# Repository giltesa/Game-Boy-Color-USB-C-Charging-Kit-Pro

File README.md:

# Game Boy Color USB-C Charging Kit PRO

The **Game Boy Color USB-C Charging Kit PRO** is the new circuit for **Nintendo Game Boy Color**. This time is all in one circuit and includes not only the **charging controller** but also a **boost converter** and **audio amplifier**.

The modern **IPS displays** with background light require more energy than the stock display. Also, **the flash cards** to load tons of games consume the battery very fast. If you really want to enjoy the games, the best way to do it is using a rechargeable battery instead of AA batteries.

However, that is not enough because a higher consume is forcing the original electronic to strive more than it can. That may cause noise in the speaker or headphones.

Typical solution has been adding a charging circuit for the battery and a power converter to replace the old and not efficiently one which is included in the GBC. Some people also add an audio amplifier to hear better the speaker sound. All these things make the GBC perfect, however the installation require a lot of cables and can not be easy for some people without enough knowledge.

Typical installation of the 3 modules:

*(Thanks Sascha for the photo of his installation!)*

For resolving that, this new **Game Boy Color USB-C Charging Kit PRO** includes the three circuits in one, everything wired each other, and you will just need to solder a few points to the GBC board.

## FEATURES

-   Exact shape for Game Boy Color.
-   Li-Ion battery charger by USB-C with protection for charging level and overdischarge.
-   DC to DC converter (only 5V output, not compatible with the original display).
-   Audio amplifier for the speaker with a potentiometer called VR1 to setup the maximum volume.
-   Integrated LED indicators on the main board, next to the USB for charging battery (red) and full battery (green). It can be disabled by the jumper SJ1.
-   External LED indicators board for playing (white), charging battery (red) and full battery (green). Optional installation.

## Would you like it?

https://shop.giltesa.com/product/game-boy-color-usb-c-charging-kit-pro/

## More

- [giltesa.com](https://giltesa.com "giltesa.com")
- [twitter.com](https://twitter.com/giltesa "twitter.com")

## Thankfulness

Thanks to [Zekfoo](https://github.com/Zekfoo/) for sharing his wonderful [project ](https://github.com/Zekfoo/CGZ) and solve some doubts I had. (v2.X)

Also, thanks to [lygte](https://lygte-info.dk) for his review of the IC [TP500](https://lygte-info.dk/review/Review%20Charger%20TP5000%204.2-3.6V%20module%20UK.html) (v2.X)

## License

This project is licensed under a **Creative Commons** license:
**[Attribution-NonCommercial-ShareAlike 4.0 International (CC BY-NC-SA 4.0) ](https://creativecommons.org/licenses/by-nc-sa/4.0/)**

Check the [LICENSE.md](LICENSE.md) for more information.

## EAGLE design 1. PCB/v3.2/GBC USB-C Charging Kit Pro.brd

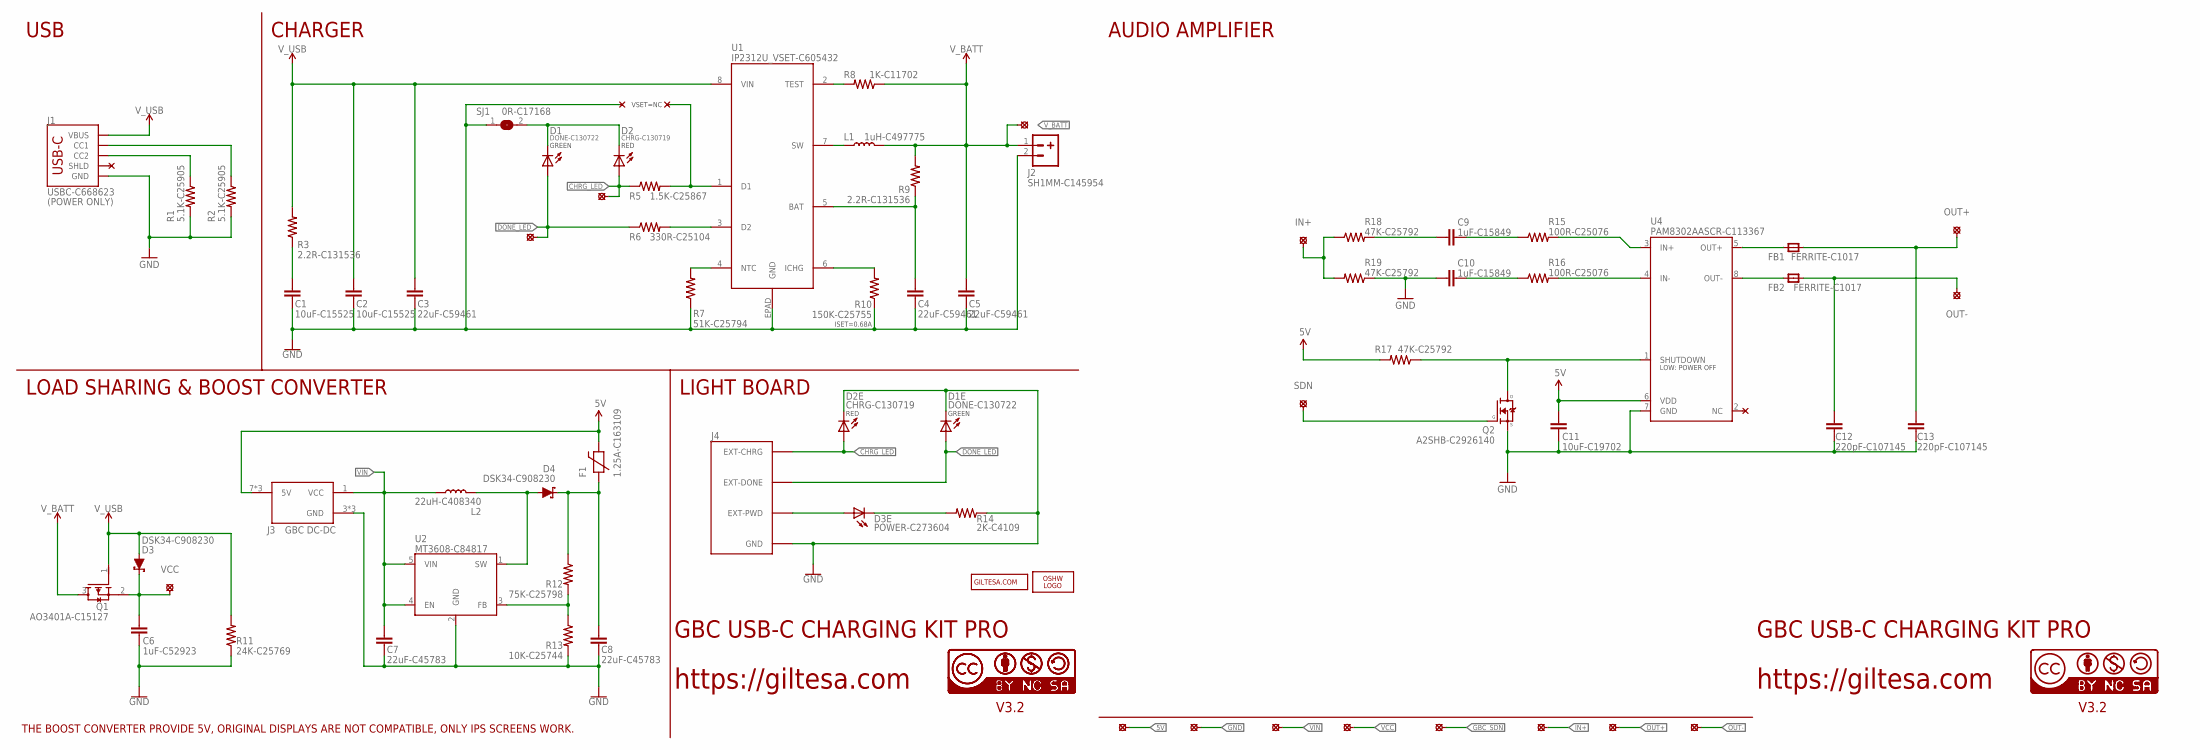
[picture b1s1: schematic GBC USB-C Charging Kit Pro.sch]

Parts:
C1, C2: 10uF-C15525; C0402_S
C3, C4, C5: 22uF-C59461; C0603_S
C6: 1uF-C52923; C0402_S
C7, C8: 22uF-C45783; C0805_S
C9, C10: 1uF-C15849; C0603_S
C11: 10uF-C19702; C0603_S
C12, C13: 220pF-C107145; C0805_S
D1, D1E: DONE-C130722; L0402
D2, D2E: CHRG-C130719; L0402
D3, D4: DSK34-C908230; SOD-123FL
D3E: POWER-C273604; L0402
F1: 1.25A-C163109; F0603_S
FB1, FB2: FERRITE-C1017; MICROBUILDER__0805MP_S
J1: USBC-C668623; USB-C_6P
J2: SH1MM-C145954; JST-2-1MM-SMD_RIGHT
J3: GBC DC-DC; GBC_DC_DC_DIP_V2
J4: GBC_LED_V2
L1: 1uH-C497775; PSPMAA0402
L2: 22uH-C408340; PSPMAA0402
LOGO2: OSHW_LOGO_FILLX0150-NT; OSHW_FILLX150_NOTEXT
PP1, PP2, PP3, PP4, PP5, PP6, PP7, PP8: SOLDER_PAD-1.5; SOLDER_PAD_1.5
Q1: AO3401A-C15127; SOT23-3_S
Q2: A2SHB-C2926140; SOT23-3_S
R1, R2: 5.1K-C25905; R0402
R3, R9: 2.2R-C131536; R0402
R5: 1.5K-C25867; R0402
R6: 330R-C25104; R0402
R7: 51K-C25794; R0402
R8: 1K-C11702; R0402
R10: 150K-C25755; R0402
R11: 24K-C25769; R0402
R12: 75K-C25798; R0402
R13: 10K-C25744; R0402
R14: 2K-C4109; R0402
R15, R16: 100R-C25076; R0402
R17, R18, R19: 47K-C25792; R0402
SJ1: 0R-C17168; JUMPER-SMD_0402
U1: IP2312U_VSET-C605432; IP2312
U2: MT3608-C84817; SOT-23-6
U4: PAM8302AASCR-C113367; PAM8302AASCR
U$1: VCC; PAD_1.25
U$2: SDN; PAD_1.0
U$3, U$24: CHRG_LED; SOLDER_PAD_1.3
U$6: CC-BY-NC-SA15MM; CC-BY-NC-SA_15MM
U$16: GILTESA.COM_MASK; GILTESA.COM_MASK_15MM
U$17, U$21: CC-NC-BCNIX; CC-NC-B_NIX
U$20: OUT+; SOLDER_PAD_2.0
U$23: OUT-; SOLDER_PAD_2.0
U$25: DONE_LED; SOLDER_PAD_1.3
U$30: IN+; SOLDER_PAD_1.3

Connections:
5V: C11.1, F1.2, J3.7 (5V), J3.7_1 (5V), J3.7_2 (5V), PP1.P$1, R17.2, U4.6 (VDD)
CHRG_LED: D2.A, D2E.A, J4.EXT-CHRG, R5.1, U$24.P$1
DONE_LED: D1.A, D1E.A, J4.EXT-DONE, R6.1, U$25.P$1
GBC_SDN: PP5.P$1, Q2.1 (G), U$2.P$1
GND: C1.1, C2.1, C3.1, C4.1, C5.1, C6.2, C7.1, C8.1, C10.2, C11.2, C12.2, C13.2, D1E.C, D2E.C, J1.A12-GND (GND), J1.B12-GND (GND), J2.2, J3.3 (GND), J3.3_1 (GND), J3.3_2 (GND), J4.GND, PP2.P$1, Q2.2 (S), R1.2, R2.2, R7.1, R10.1, R11.1, R13.2, R14.1, R19.1, SJ1.1, U1.EPAD (GND), U2.2 (GND), U4.7 (GND)
IN+: PP6.P$1, R18.1, R19.2, U$30.P$1
unnamed: D1.C, D2.C, SJ1.2
unnamed: C8.2, D4.C, F1.1, R12.1
unnamed: D4.A, L2.P$2 (2), U2.1 (SW)
unnamed: J1.B5 (CC2), R1.1
unnamed: R8.2, U1.2 (TEST)
unnamed: R12.2, R13.1, U2.3 (FB)
unnamed: R16.2, U4.4 (IN-)
unnamed: D3E.A, J4.EXT-PWD
unnamed: D3E.C, R14.2
unnamed: R15.2, U4.3 (IN+)
unnamed: J1.A5 (CC1), R2.1
unnamed: C4.2, R9.1, U1.5 (BAT)
unnamed: C1.2, R3.1
unnamed: C10.1, R16.1
unnamed: FB2.1, U4.8 (OUT-)
unnamed: R5.2, U1.1 (D1)
unnamed: FB1.1, U4.5 (OUT+)
unnamed: C9.1, R15.1
unnamed: C9.2, R18.2
unnamed: R7.2, U1.4 (NTC)
unnamed: R10.2, U1.6 (ICHG)
unnamed: R6.2, U1.3 (D2)
unnamed: L1.P$1 (1), U1.7 (SW)
OUT+: C13.1, FB1.2, PP7.P$1, U$20.P$1
OUT-: C12.1, FB2.2, PP8.P$1, U$23.P$1
SDN: Q2.3 (D), R17.1, U4.1 (SHUTDOWN)
VCC: C6.1, D3.C, PP4.P$1, Q1.2 (S), U$1.P$1
VIN: C7.2, J3.1 (VCC), L2.P$1 (1), PP3.P$1, U2.4 (EN), U2.5 (VIN)
V_BATT: C5.2, J2.1, L1.P$2 (2), Q1.3 (D), R8.1, R9.2, U$3.P$1
V_USB: C2.2, C3.2, D3.A, J1.A9-VBUS (VBUS), J1.B9-VBUS (VBUS), Q1.1 (G), R3.2, R11.2, U1.8 (VIN)

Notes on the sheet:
GBC USB-C CHARGING KIT PRO
https://giltesa.com
V3.2
(POWER ONLY)
THE BOOST CONVERTER PROVIDE 5V, ORIGINAL DISPLAYS ARE NOT COMPATIBLE, ONLY IPS SCREENS WORK.
USB
CHARGER
LOAD SHARING & BOOST CONVERTER
AUDIO AMPLIFIER
LIGHT BOARD
ISET=0.68A
GREEN
RED
VSET=NC

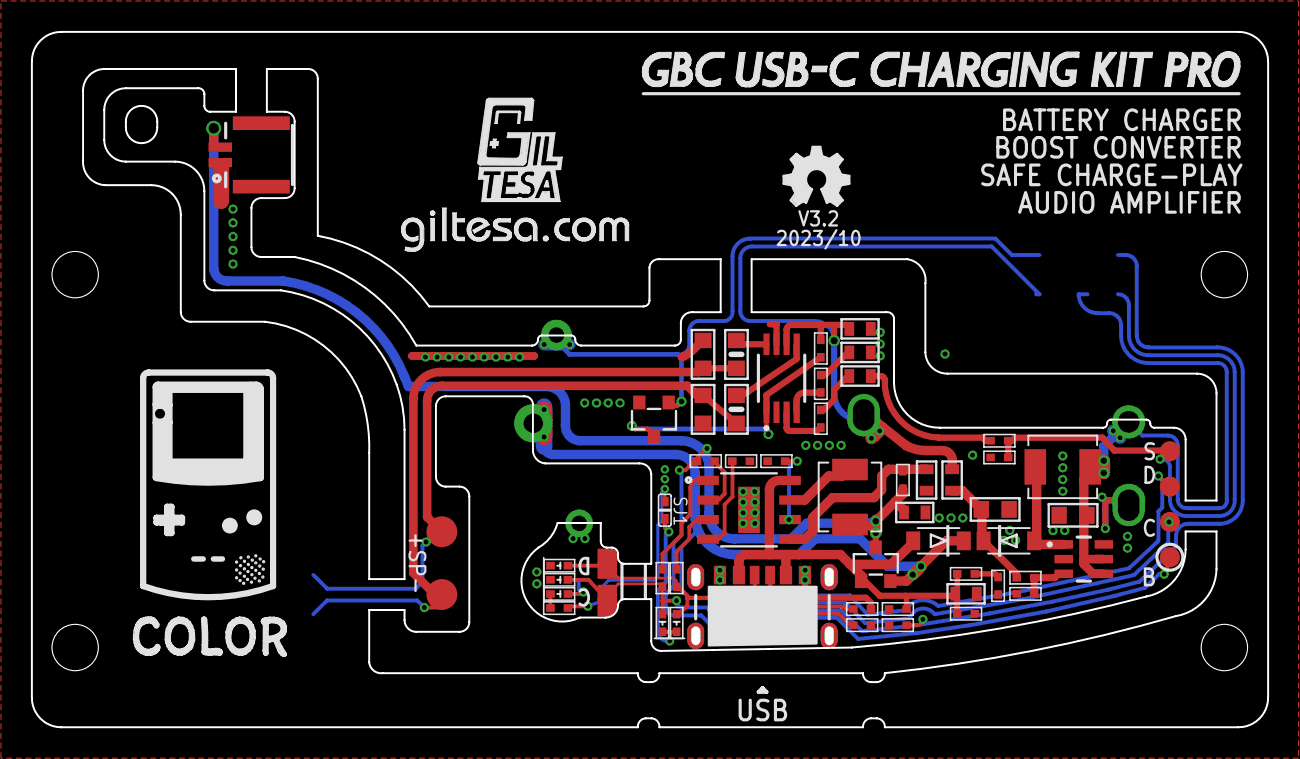
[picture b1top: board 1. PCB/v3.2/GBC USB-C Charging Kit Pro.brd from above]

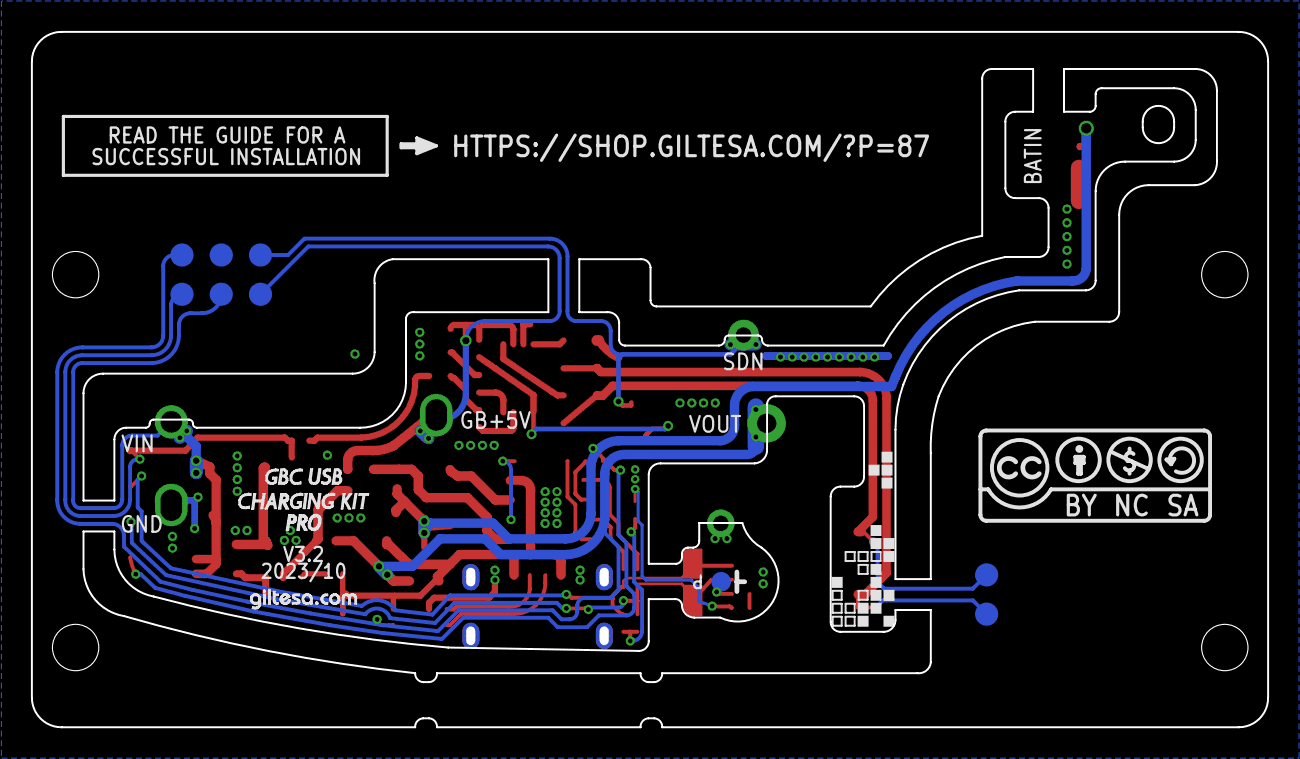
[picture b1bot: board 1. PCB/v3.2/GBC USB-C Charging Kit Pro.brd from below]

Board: 2 copper layers, 80.0 x 45.0 mm, 80 parts (11 on the bottom side), 36 nets.

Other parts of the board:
U$7: GBC_FRAME_LOGO
U$9: GILTESA_LOGO_MASK_7MM
U$10: TETRIS
U$12: GBC_PRO_FRAME
U$33: GILTESA.COM_MASK_7MM@1
U$34: GAME_BOY_COLOR_USB_CHARGING_KIT_PRO

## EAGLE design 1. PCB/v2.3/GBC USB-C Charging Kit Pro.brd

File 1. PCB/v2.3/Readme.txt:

2023-02-12: GBC PRO v2.3

It recently has been detected a strange malfunction
that can occur only in this specific situation and not always,
it happens occasionally:

    With the GBC turned off, you plug in the USB-C cable and then power on the GBC.
    Occasionally the red light will turn off just after the GBC is turned on,
    and then the charging circuit will get very hot until it is damaged.

    It works properly when the GBC is already on and then the USB-C cable is connected.
    Or when the GBC is charging but it remains off.
    https://www.youtube.com/watch?v=xmc3yf6yNuk

However, I highly recommend not charging and playing at the same time to avoid any problem
(like the previous version which didn’t support it).

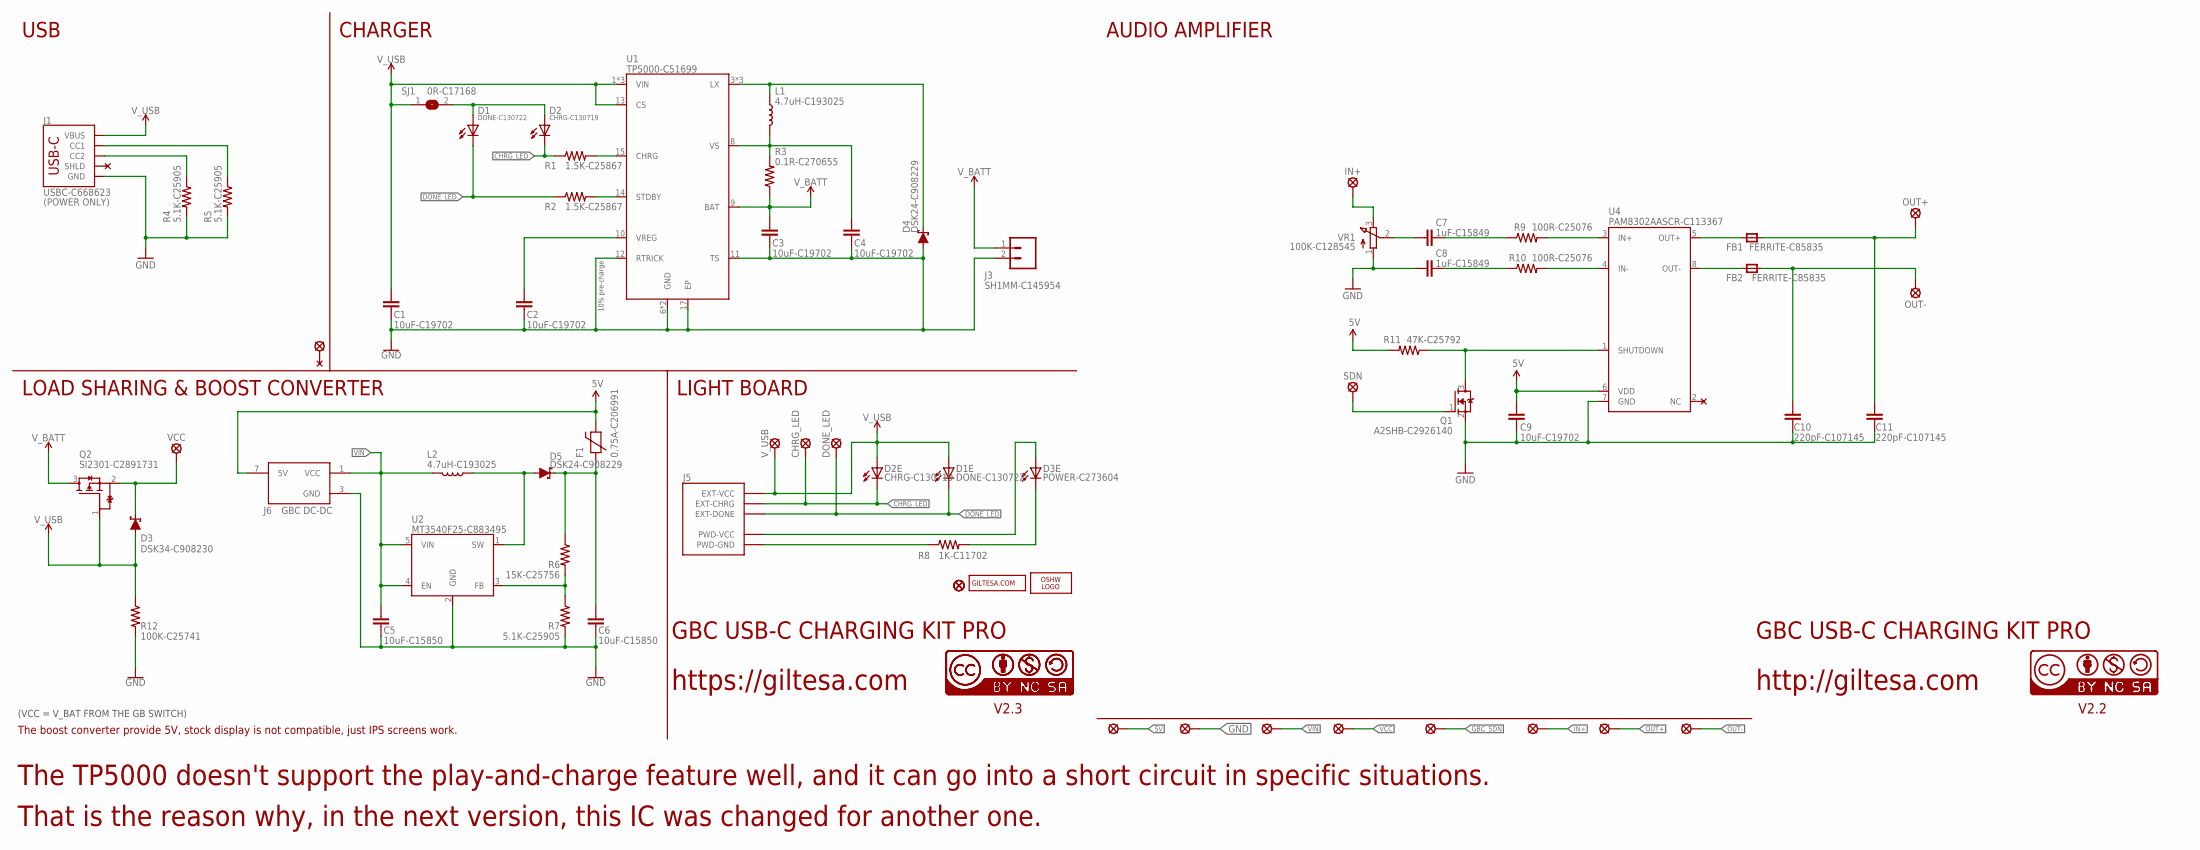
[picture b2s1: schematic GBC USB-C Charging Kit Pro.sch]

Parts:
C1, C2, C3, C4, C9: 10uF-C19702; C0603_S
C5, C6: 10uF-C15850; C0805_S
C7, C8: 1uF-C15849; C0603_S
C10, C11: 220pF-C107145; C0805_S
D1, D1E: DONE-C130722; L0402
D2, D2E: CHRG-C130719; L0402
D3: DSK34-C908230; SOD-123FL
D3E: POWER-C273604; L0402
D4, D5: DSK24-C908229; SOD-123FL
F1: 0.75A-C206991; F0603_S
FB1, FB2: FERRITE-C85835; MICROBUILDER__0805MP_S
FD1, FD2, FD3: FIDUCIALUFIDUCIAL; FIDUCIAL-MICRO
J1: USBC-C668623; USB-C_6P
J3: SH1MM-C145954; JST-2-1MM-SMD_RIGHT
J5: GBC_LED
J6: GBC DC-DC; GBC_DC_DC_DIP
L1, L2: 4.7uH-C193025; PSPMAA0402
LOGO2: OSHW_LOGO_FILLX0150-NT; OSHW_FILLX150_NOTEXT
PP1, PP2, PP3, PP4, PP5, PP6, PP7, PP8: SOLDER_PAD-1.5; SOLDER_PAD_1.5
Q1: A2SHB-C2926140; SOT23-3_S
Q2: SI2301-C2891731; SOT23-3_S
R1, R2: 1.5K-C25867; R0402
R3: 0.1R-C270655; R0402
R4, R5, R7: 5.1K-C25905; R0402
R6: 15K-C25756; R0402
R8: 1K-C11702; R0402
R9, R10: 100R-C25076; R0402
R11: 47K-C25792; R0402
R12: 100K-C25741; R0402
SJ1: 0R-C17168; JUMPER-SMD_0402
U1: TP5000-C51699; QFN-16_4X4
U2: MT3540F25-C883495; SOT-23-5
U4: PAM8302AASCR-C113367; PAM8302AASCR
U$2: SDN; PAD_1.0
U$6: CC-BY-NC-SA15MM; CC-BY-NC-SA_15MM
U$16: GILTESA.COM_MASK
U$17, U$21: CC-NC-BCNIX; CC-NC-B_NIX
U$20: OUT+; SOLDER_PAD_2.0
U$23: OUT-; SOLDER_PAD_2.0
U$24: CHRG_LED; SOLDER_PAD_1.3
U$25: DONE_LED; SOLDER_PAD_1.3
U$26: V_USB; SOLDER_PAD_1.3
U$29: VCC; PAD_1.25
U$30: IN+; SOLDER_PAD_1.3
U$32: SOLDER_PAD-2.5; SOLDER_PAD_2.5
VR1: 100K-C128545; TRIMPOT_BOURNS_3303W

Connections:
5V: C9.1, F1.2, J6.7 (5V), PP1.P$1, R11.2, U4.6 (VDD)
CHRG_LED: D2.C, D2E.C, J5.EXT-CHRG, R1.1, U$24.P$1
DONE_LED: D1.C, D1E.C, J5.EXT-DONE, R2.1, U$25.P$1
GBC_SDN: PP5.P$1, Q1.1 (G), U$2.P$1
GND: C1.1, C2.1, C3.1, C4.1, C5.1, C6.1, C8.2, C9.2, C10.2, C11.2, D4.A, J1.GND1 (GND), J1.GND2 (GND), J3.2, J6.3 (GND), PP2.P$1, Q1.2 (S), R4.2, R5.2, R7.2, R12.2, U1.6 (GND), U1.7 (GND), U1.11 (TS), U1.12 (RTRICK), U1.17 (EP), U2.2 (GND), U4.7 (GND), VR1.1 (A)
IN+: PP6.P$1, U$30.P$1, VR1.3 (E)
unnamed: D1.A, D2.A, SJ1.2
unnamed: C6.2, D5.C, F1.1, R6.1
unnamed: D5.A, L2.P$1 (1), U2.1 (SW)
unnamed: J1.B5 (CC2), R4.1
unnamed: R1.2, U1.15 (CHRG)
unnamed: R6.2, R7.1, U2.3 (FB)
unnamed: J5.PWD-GND, R8.1
unnamed: R10.2, U4.4 (IN-)
unnamed: D3E.A, J5.PWD-VCC
unnamed: D3E.C, R8.2
unnamed: R9.2, U4.3 (IN+)
unnamed: J1.A5 (CC1), R5.1
unnamed: C8.1, R10.1
unnamed: FB2.1, U4.8 (OUT-)
unnamed: C2.2, U1.10 (VREG)
unnamed: R2.2, U1.14 (STDBY)
unnamed: C4.2, L1.P$2 (2), R3.2, U1.8 (VS)
unnamed: D4.C, L1.P$1 (1), U1.3 (LX), U1.4 (LX), U1.5 (LX)
unnamed: FB1.1, U4.5 (OUT+)
unnamed: C7.1, R9.1
unnamed: C7.2, VR1.2 (S)
OUT+: C11.1, FB1.2, PP7.P$1, U$20.P$1
OUT-: C10.1, FB2.2, PP8.P$1, U$23.P$1
SDN: Q1.3 (D), R11.1, U4.1 (SHUTDOWN)
VCC: D3.C, PP4.P$1, Q2.2 (S), U$29.P$1
VIN: C5.2, J6.1 (VCC), L2.P$2 (2), PP3.P$1, U2.4 (EN), U2.5 (VIN)
V_BATT: C3.2, J3.1, Q2.3 (D), R3.1, U1.9 (BAT)
V_USB: C1.2, D1E.A, D2E.A, D3.A, J1.VBUS1 (VBUS), J1.VBUS2 (VBUS), J5.EXT-VCC, Q2.1 (G), R12.1, SJ1.1, U1.1 (VIN), U1.2 (VIN), U1.13 (CS), U1.16 (VIN), U$26.P$1

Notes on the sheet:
GBC USB-C CHARGING KIT PRO
https://giltesa.com
V2.3
(POWER ONLY)
The boost converter provide 5V, stock display is not compatible, just IPS screens work.
(VCC = V_BAT FROM THE GB SWITCH)
USB
CHARGER
LOAD SHARING & BOOST CONVERTER
AUDIO AMPLIFIER
http://giltesa.com
V2.2
10% pre-charge
LIGHT BOARD
The TP5000 doesn't support the play-and-charge feature well, and it can go into a short circuit in specific situations.
That is the reason why, in the next version, this IC was changed for another one.

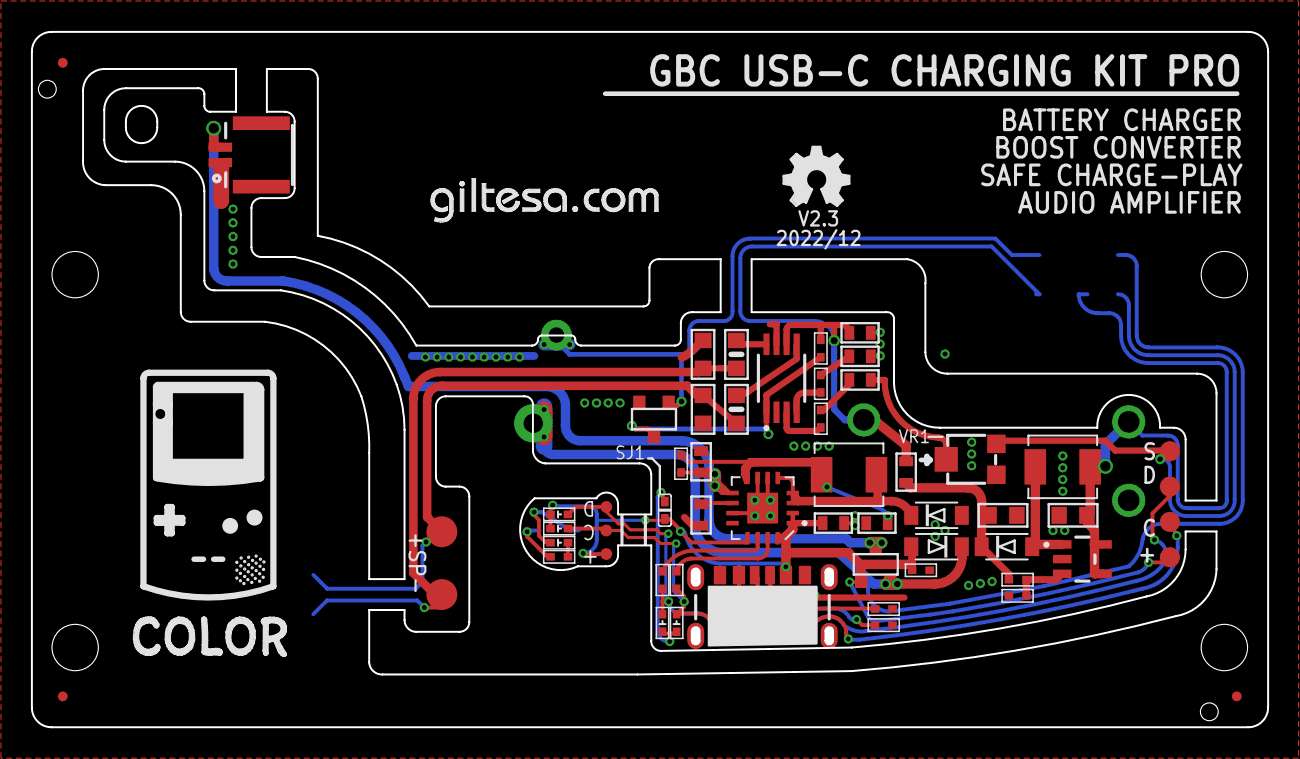
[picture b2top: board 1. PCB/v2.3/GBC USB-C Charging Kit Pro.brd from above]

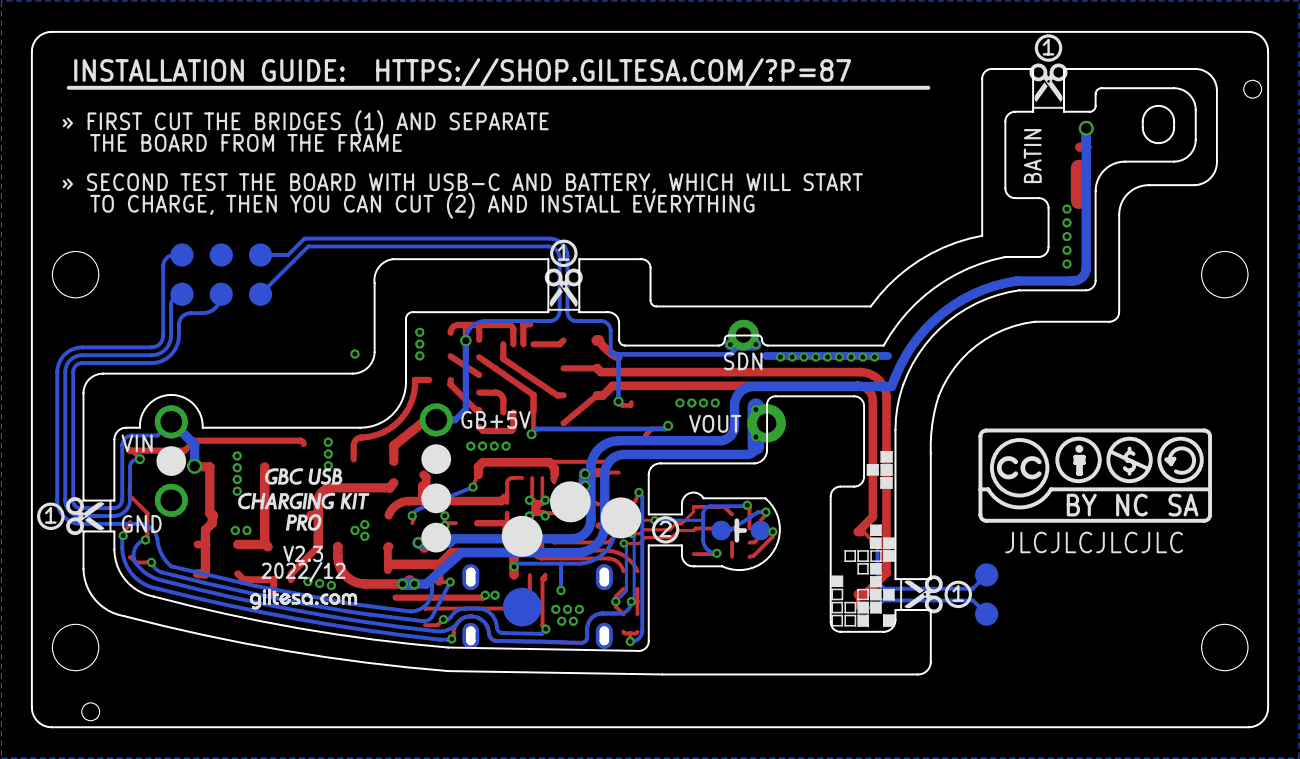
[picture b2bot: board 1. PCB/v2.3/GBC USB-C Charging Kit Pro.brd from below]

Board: 2 copper layers, 80.0 x 45.0 mm, 88 parts (21 on the bottom side), 34 nets.

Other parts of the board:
U$7: GAME_BOY_COLOR_1.2
U$8, U$13, U$14, U$15: SCISSOR
U$10: TETRIS
U$12, U$18: JLCPCB_TOOLING_HOLES
U$28: GAME_BOY_COLOR_2
U$33: GILTESA.COM_MASK_7MM
U$34: GAME_BOY_COLOR_USB_CHARGING_KIT_PRO
U$36, U$37, U$38, U$39: SCISSOR_ONE
U$40: SCISSOR_TWO

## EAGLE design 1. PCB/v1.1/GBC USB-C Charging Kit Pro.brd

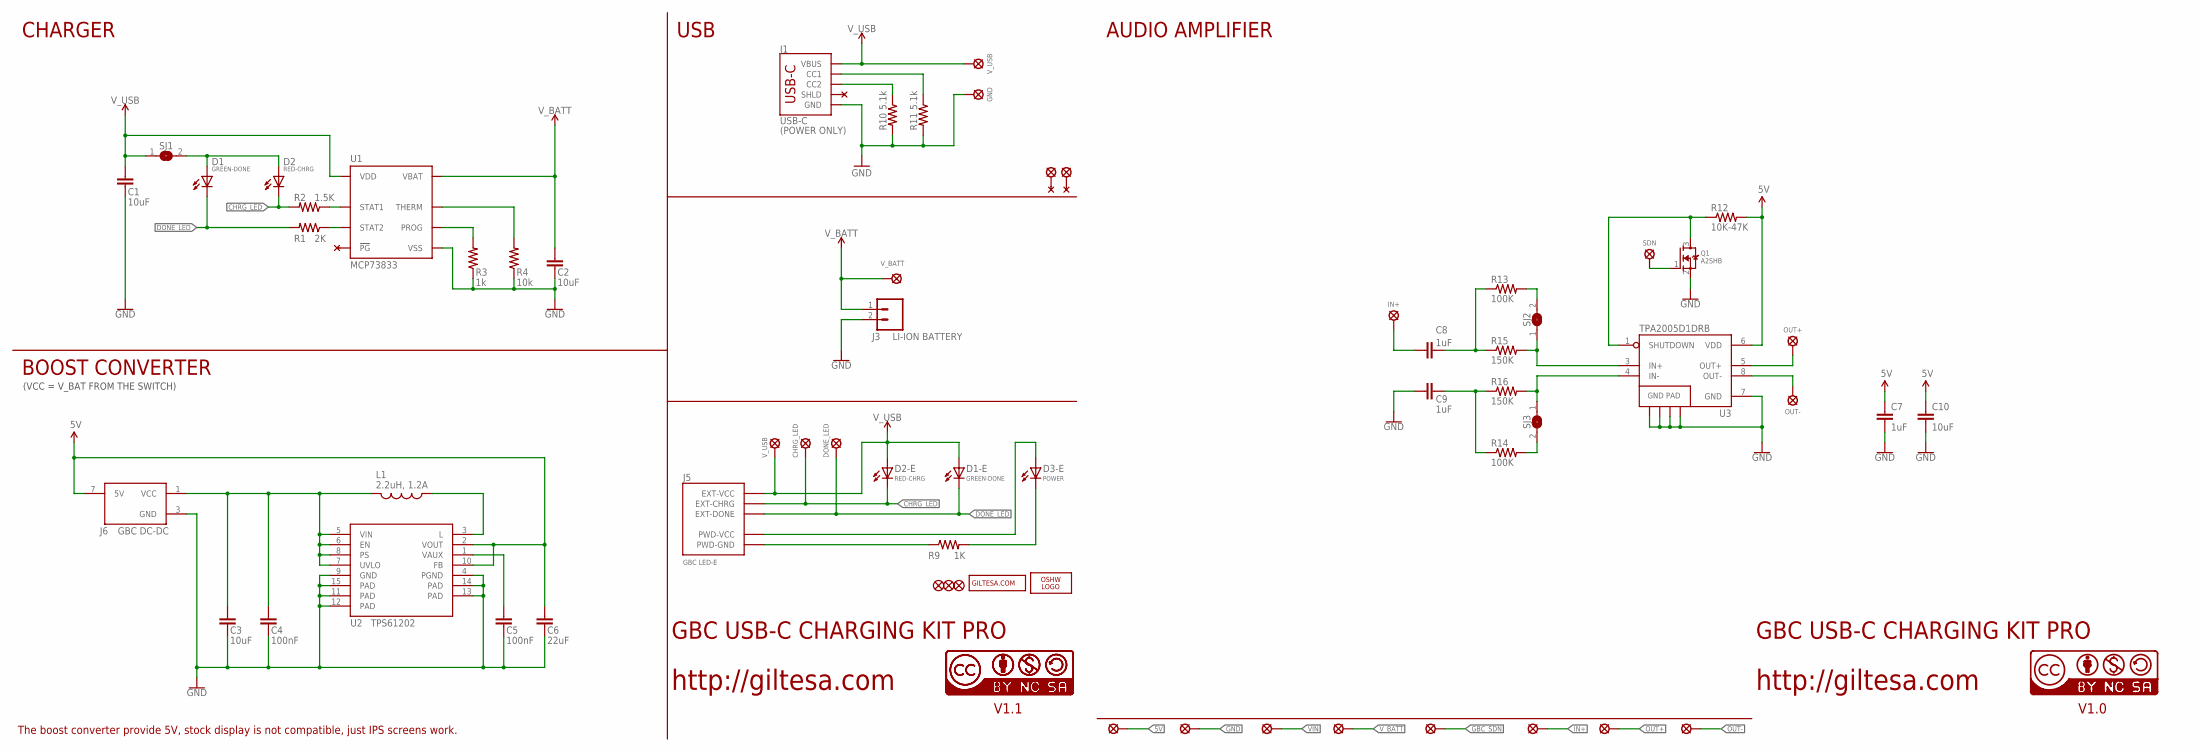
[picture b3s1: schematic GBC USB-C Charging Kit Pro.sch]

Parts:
C1, C2: 10uF; C0603
C3, C10: 10uF; C1206
C4, C5: 100nF; C0603
C6: 22uF; C0805_S
C7: 1uF; C1206
C8, C9: 1uF; C0402
D1, D1-E: GREEN-DONE; L0402
D2, D2-E: RED-CHRG; L0402
D3-E: POWER; L0402
FD2, FD3, FD4: FIDUCIALUFIDUCIAL; FIDUCIAL-MICRO
J1: USB-C; USB-C_6P
J3: LI-ION BATTERY; JST-2-1MM-SMD_RIGHT
J5: GBC LED-E; GBC_LED
J6: GBC DC-DC; GBC_DC_DC_DIP
L1: 2.2uH, 1.2A; CDRH2D09
LOGO2: OSHW_LOGO_FILLX0150-NT; OSHW_FILLX150_NOTEXT
PP1, PP2, PP3, PP4, PP5, PP6, PP7, PP8: SOLDER_PAD-1.5; SOLDER_PAD_1.5
Q1: A2SHB; SOT23
R1: 2K; R0402
R2: 1.5K; R0402
R3: 1k; R0402
R4: 10k; R0402
R9: 1K; R0402
R10, R11: 5.1k; R0402
R12: 10K-47K; R0402
R13, R14: 100K; R0402
R15, R16: 150K; R0402
SJ1, SJ2, SJ3: JUMPER-SMD0402; JUMPER-SMD_0402
U1: MCP73833; DFN-10
U2: TPS61202; QFN-10_PAD
U3: TPA2005D1DRB; QFN-8_PAD
U$1: V_USB; SOLDER_PAD_1.5
U$2: SDN; PAD_1.0
U$3: GND; SOLDER_PAD_1.5
U$6: CC-BY-NC-SA15MM; CC-BY-NC-SA_15MM
U$9, U$32: SOLDER_PAD-2.5; SOLDER_PAD_2.5
U$16: GILTESA.COM_MASK
U$17, U$21: CC-NC-BCNIX; CC-NC-B_NIX
U$20: OUT+; SOLDER_PAD_2.0
U$23: OUT-; SOLDER_PAD_2.0
U$24: CHRG_LED; SOLDER_PAD_1.3
U$25: DONE_LED; SOLDER_PAD_1.3
U$26: V_USB; SOLDER_PAD_1.3
U$29: V_BATT; PAD_1.25
U$30: IN+; SOLDER_PAD_1.3

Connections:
5V: C6.1, C7.1, C10.1, J6.7 (5V), PP1.P$1, R12.2, U2.2 (VOUT), U2.10 (FB), U3.6 (VDD)
CHRG_LED: D2.C, D2-E.C, J5.EXT-CHRG, R2.2, U$24.P$1
DONE_LED: D1.C, D1-E.C, J5.EXT-DONE, R1.2, U$25.P$1
GBC_SDN: PP5.P$1, Q1.1 (G), U$2.P$1
GND: C1.2, C2.2, C3.2, C4.2, C5.2, C6.2, C7.2, C9.1, C10.2, J1.GND1 (GND), J1.GND2 (GND), J3.2, J6.3 (GND), PP2.P$1, Q1.2 (S), R3.1, R4.1, R10.2, R11.2, U1.P$5 (VSS), U1.P$11 (VSS), U2.4 (PGND), U2.9 (GND), U2.11 (PAD), U2.12 (PAD), U2.13 (PAD), U2.14 (PAD), U2.15 (PAD), U3.7 (GND), U3.10 (GND), U3.11 (GND), U3.12 (GND), U3.13 (GND), U$3.P$1
IN+: C8.1, PP6.P$1, U$30.P$1
IN+AMP: R15.2, SJ2.1, U3.3 (IN+)
IN-AMP: R16.2, SJ3.1, U3.4 (IN-)
unnamed: D1.A, D2.A, SJ1.2
unnamed: R13.2, SJ2.2
unnamed: L1.P$1 (1), U2.3 (L)
unnamed: J1.B5 (CC2), R10.1
unnamed: R14.2, SJ3.2
unnamed: C5.1, U2.1 (VAUX)
unnamed: J5.PWD-GND, R9.1
unnamed: D3-E.A, J5.PWD-VCC
unnamed: D3-E.C, R9.2
unnamed: J1.A5 (CC1), R11.1
unnamed: C8.2, R13.1, R15.1
unnamed: C9.2, R14.1, R16.1
OUT+: PP7.P$1, U3.5 (OUT+), U$20.P$1
OUT-: PP8.P$1, U3.8 (OUT-), U$23.P$1
PROG: R3.2, U1.P$6 (PROG)
SDN: Q1.3 (D), R12.1, U3.1 (SHUTDOWN)
STAT1: R2.1, U1.P$3 (STAT1)
STAT2: R1.1, U1.P$4 (STAT2)
THERM: R4.2, U1.P$8 (THERM)
VIN: C3.1, C4.1, J6.1 (VCC), L1.P$2 (2), PP3.P$1, U2.5 (VIN), U2.6 (EN), U2.7 (UVLO), U2.8 (PS)
V_BATT: C2.1, J3.1, PP4.P$1, U1.P$9 (VBAT), U1.P$10 (VBAT), U$29.P$1
V_USB: C1.1, D1-E.A, D2-E.A, J1.VBUS1 (VBUS), J1.VBUS2 (VBUS), J5.EXT-VCC, SJ1.1, U1.P$1 (VDD), U1.P$2 (VDD), U$1.P$1, U$26.P$1

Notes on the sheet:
GBC USB-C CHARGING KIT PRO
http://giltesa.com
V1.1
(POWER ONLY)
The boost converter provide 5V, stock display is not compatible, just IPS screens work.
(VCC = V_BAT FROM THE SWITCH)
USB
CHARGER
BOOST CONVERTER
AUDIO AMPLIFIER
V1.0

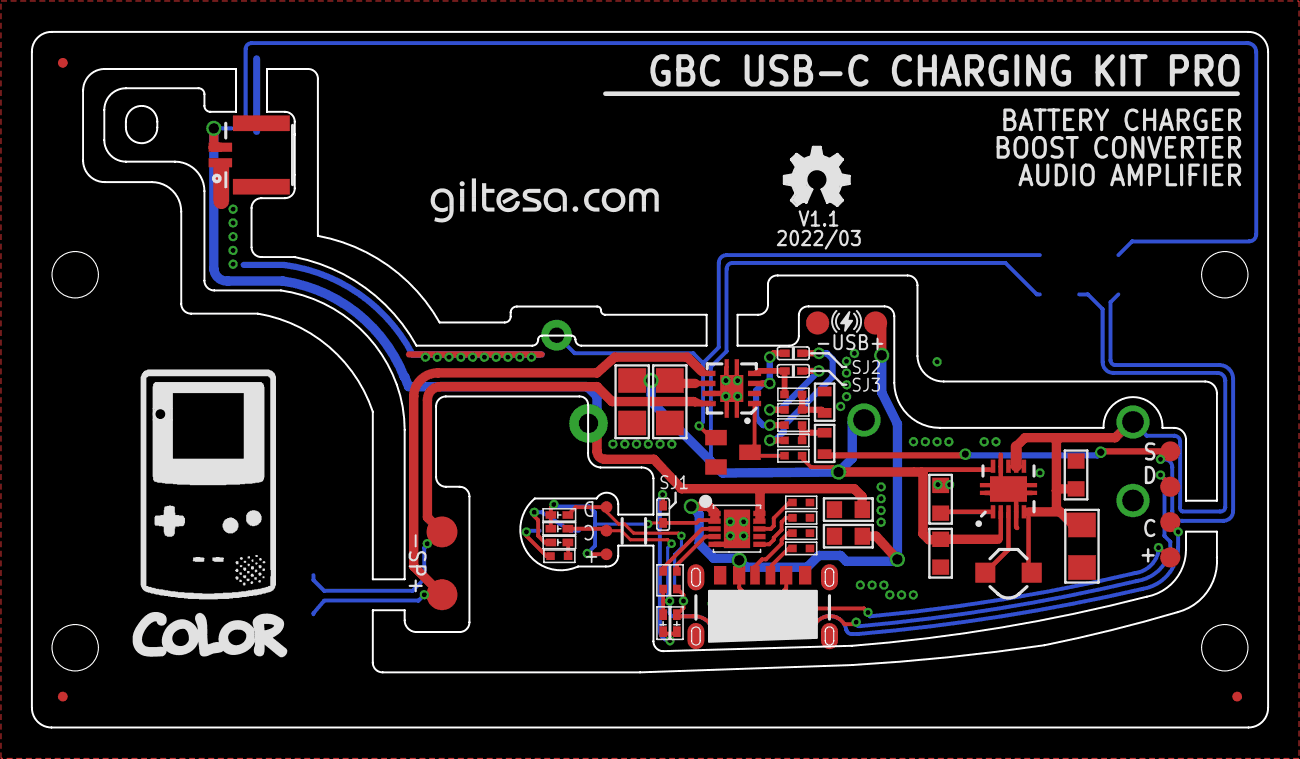
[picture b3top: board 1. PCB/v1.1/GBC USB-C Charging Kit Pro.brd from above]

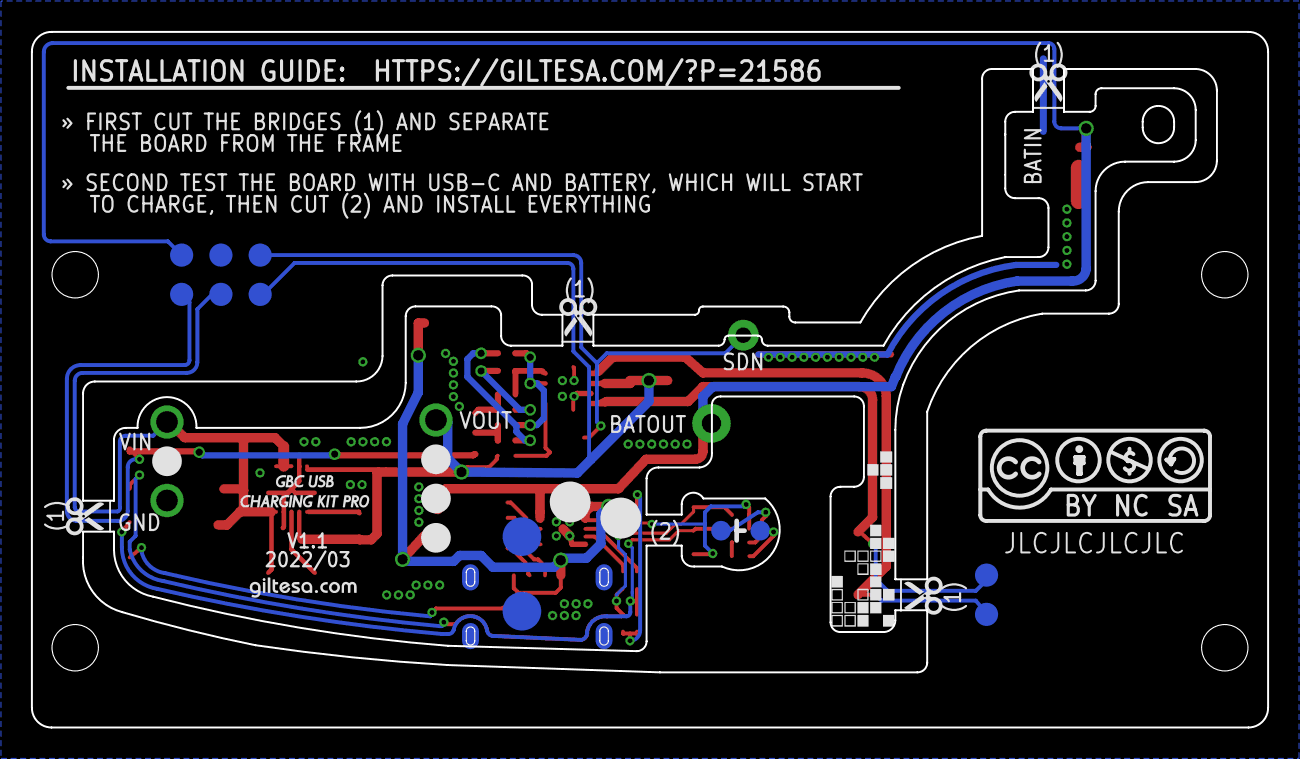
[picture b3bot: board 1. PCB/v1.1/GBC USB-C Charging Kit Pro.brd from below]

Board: 2 copper layers, 80.0 x 45.0 mm, 77 parts (17 on the bottom side), 30 nets.

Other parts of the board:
U$7: GAME_BOY_COLOR
U$8, U$13, U$14, U$15: SCISSOR
U$10: TETRIS
U$19: QI
U$28: GAME_BOY_COLOR_2
U$33: GILTESA.COM_MASK_7MM
U$34: GAME_BOY_COLOR_USB_CHARGING_KIT_PRO

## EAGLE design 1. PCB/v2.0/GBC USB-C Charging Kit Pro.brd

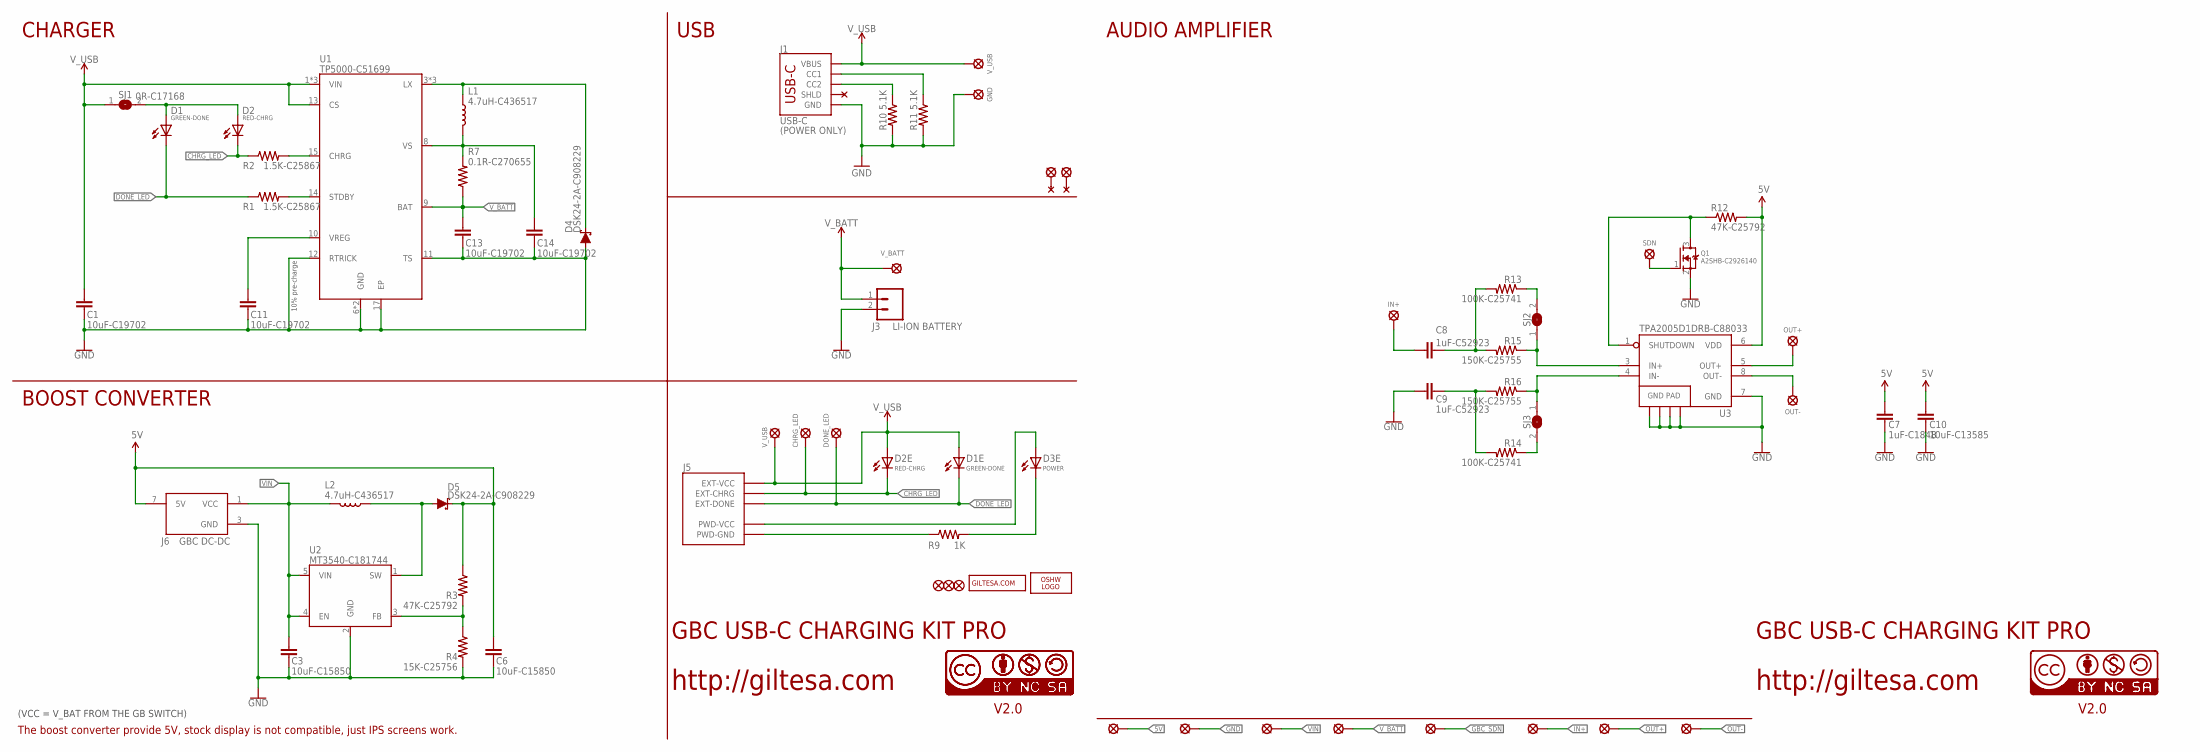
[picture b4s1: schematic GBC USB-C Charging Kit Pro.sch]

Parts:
C1, C11, C13, C14: 10uF-C19702; C0603_S
C3, C6: 10uF-C15850; C0805_S
C7: 1uF-C1848; C1206
C8, C9: 1uF-C52923; C0603_S
C10: 10uF-C13585; C1206
D1, D1E: GREEN-DONE; L0402
D2, D2E: RED-CHRG; L0402
D3E: POWER; L0402
D4, D5: DSK24-2A-C908229; SOD-123FL
FD2, FD3, FD4: FIDUCIALUFIDUCIAL; FIDUCIAL-MICRO
J1: USB-C; USB-C_6P
J3: LI-ION BATTERY; JST-2-1MM-SMD_RIGHT
J5: GBC_LED
J6: GBC DC-DC; GBC_DC_DC_DIP
L1, L2: 4.7uH-C436517; PSPMAA0402
LOGO2: OSHW_LOGO_FILLX0150-NT; OSHW_FILLX150_NOTEXT
PP1, PP2, PP3, PP4, PP5, PP6, PP7, PP8: SOLDER_PAD-1.5; SOLDER_PAD_1.5
Q1: A2SHB-C2926140; SOT23-3_S
R1, R2: 1.5K-C25867; R0402
R3, R12: 47K-C25792; R0402
R4: 15K-C25756; R0402
R7: 0.1R-C270655; R0402
R9: 1K; R0402
R10, R11: 5.1K; R0402
R13, R14: 100K-C25741; R0402
R15, R16: 150K-C25755; R0402
SJ1: 0R-C17168; JUMPER-SMD_0402
SJ2, SJ3: JUMPER-SMD0402; JUMPER-SMD_0402
U1: TP5000-C51699; QFN-16_4X4
U2: MT3540-C181744; SOT-23-5
U3: TPA2005D1DRB-C88033; QFN-8_PAD
U$1: V_USB; SOLDER_PAD_1.5
U$2: SDN; PAD_1.0
U$3: GND; SOLDER_PAD_1.5
U$6: CC-BY-NC-SA15MM; CC-BY-NC-SA_15MM
U$9, U$32: SOLDER_PAD-2.5; SOLDER_PAD_2.5
U$16: GILTESA.COM_MASK
U$17, U$21: CC-NC-BCNIX; CC-NC-B_NIX
U$20: OUT+; SOLDER_PAD_2.0
U$23: OUT-; SOLDER_PAD_2.0
U$24: CHRG_LED; SOLDER_PAD_1.3
U$25: DONE_LED; SOLDER_PAD_1.3
U$26: V_USB; SOLDER_PAD_1.3
U$29: V_BATT; PAD_1.25
U$30: IN+; SOLDER_PAD_1.3

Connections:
5V: C6.2, C7.2, C10.2, D5.C, J6.7 (5V), PP1.P$1, R3.1, R12.2, U3.6 (VDD)
CHRG_LED: D2.C, D2E.C, J5.EXT-CHRG, R2.1, U$24.P$1
DONE_LED: D1.C, D1E.C, J5.EXT-DONE, R1.1, U$25.P$1
GBC_SDN: PP5.P$1, Q1.1 (G), U$2.P$1
GND: C1.1, C3.1, C6.1, C7.1, C9.2, C10.1, C11.1, C13.1, C14.1, D4.A, J1.GND1 (GND), J1.GND2 (GND), J3.2, J6.3 (GND), PP2.P$1, Q1.2 (S), R4.2, R10.2, R11.2, U1.6 (GND), U1.7 (GND), U1.11 (TS), U1.12 (RTRICK), U1.17 (EP), U2.2 (GND), U3.7 (GND), U3.10 (GND), U3.11 (GND), U3.12 (GND), U3.13 (GND), U$3.P$1
IN+: C8.1, PP6.P$1, U$30.P$1
IN+AMP: R15.1, SJ2.1, U3.3 (IN+)
IN-AMP: R16.1, SJ3.1, U3.4 (IN-)
unnamed: D1.A, D2.A, SJ1.2
unnamed: R13.1, SJ2.2
unnamed: D5.A, L2.P$1 (1), U2.1 (SW)
unnamed: J1.B5 (CC2), R10.1
unnamed: R14.1, SJ3.2
unnamed: R2.2, U1.15 (CHRG)
unnamed: R3.2, R4.1, U2.3 (FB)
unnamed: J5.PWD-GND, R9.1
unnamed: D3E.A, J5.PWD-VCC
unnamed: D3E.C, R9.2
unnamed: J1.A5 (CC1), R11.1
unnamed: C8.2, R13.2, R15.2
unnamed: C9.1, R14.2, R16.2
unnamed: C11.2, U1.10 (VREG)
unnamed: R1.2, U1.14 (STDBY)
unnamed: C14.2, L1.P$2 (2), R7.2, U1.8 (VS)
unnamed: D4.C, L1.P$1 (1), U1.3 (LX), U1.4 (LX), U1.5 (LX)
OUT+: PP7.P$1, U3.5 (OUT+), U$20.P$1
OUT-: PP8.P$1, U3.8 (OUT-), U$23.P$1
SDN: Q1.3 (D), R12.1, U3.1 (SHUTDOWN)
VIN: C3.2, J6.1 (VCC), L2.P$2 (2), PP3.P$1, U2.4 (EN), U2.5 (VIN)
V_BATT: C13.2, J3.1, PP4.P$1, R7.1, U1.9 (BAT), U$29.P$1
V_USB: C1.2, D1E.A, D2E.A, J1.VBUS1 (VBUS), J1.VBUS2 (VBUS), J5.EXT-VCC, SJ1.1, U1.1 (VIN), U1.2 (VIN), U1.13 (CS), U1.16 (VIN), U$1.P$1, U$26.P$1

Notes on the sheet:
GBC USB-C CHARGING KIT PRO
http://giltesa.com
V2.0
(POWER ONLY)
The boost converter provide 5V, stock display is not compatible, just IPS screens work.
(VCC = V_BAT FROM THE GB SWITCH)
USB
CHARGER
BOOST CONVERTER
AUDIO AMPLIFIER
10% pre-charge

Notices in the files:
parts and their libraries:
SparkFun: Licensing: CC v3.0 Share-Alike You are welcome to use this library for commercial purposes.
SparkFun-PowerSymbols: Licensing: Creative Commons ShareAlike 4.0 International - https://creativecommons.org/licenses/by-sa/4.0
cc-by-nc-sa: All hardware is licensed under the Creative Commons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
